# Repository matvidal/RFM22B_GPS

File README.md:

# RFM22B_GPS
In this repository you can find multiple tests using the transceiver RFM22B and the L80 GPS. Given that both devices use a logic level of 3.3 V, they are both connected to an Arduino Due board. 

The echo test is used to try different combinations of bit rate and modulation at different distances and analize which combination permorms better. The purpose of the GPS test is to determine which is the maximum distance that this transceiver can reach with uncorrupted data using the best configuration obtained before. In order to do that, a GPS is added to obtain at what distance the communication link is lost.

The GPS test consists on using a radiosonde to transport one Arduino Due, one GPS L80 and one RFM22B acting as a transmiter. On the ground there will be three RFM22B with arduinos to receive the data from the GPS. One will use an omnidirectional antenna, another a personal Yagi antenna, and the third will be connected to the Earth Station of the Department of Electrical Engineering of Universidad de Chile.

## Code
In this folder you will find some tests you can run using the Radiohead library for the transceiver and the TinyGPS+ library for the GPS.

### Chat test
Two Arduinos are hooked up to two different computers. Using the serial monitor, two persons can write messages to each other and send them using the transceiver RFM22B.

### Normal test
One transceiver is the transmiter and the other the receiver. Random packets are sent continually from TX to RX. If there is no confirmation of the packet being received correctly by the RX, an error message is printed on screen.

### Echo test
In this test, one Arduino generates 1000 packets of random data and transmit it to another Arduino. Then, the receiver only retransmit the same packet to the TX. The TX compares the data generated and the packet received and evaluates if they are the same and use a counter to save the number of successes.
 
### GPS test

The transmiter with the microcontroler and the GPS is transported by a balloon with helium. It transmit the data adquired by the GPS to three different receivers.

## Doc
All the datasheets of the components used are in this folder. There is also an .ods file with the results of the radiosonde test.

## Hardware
Here there are all the designs of the shields to plug the breakout board of the RFM22B to the Arduino Due, the GPS with the TRX and the arduino and the RFM23BP transceiver to also an Arduino Due.

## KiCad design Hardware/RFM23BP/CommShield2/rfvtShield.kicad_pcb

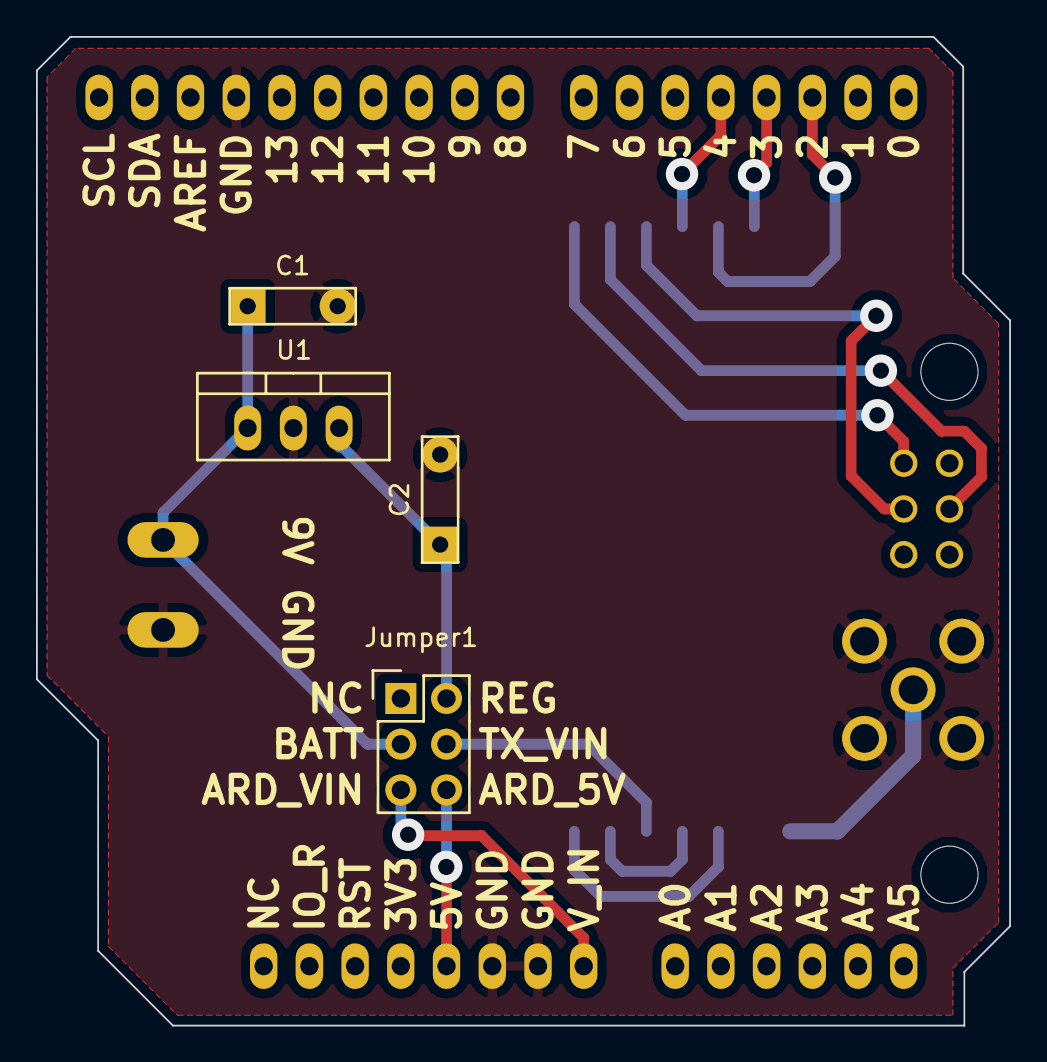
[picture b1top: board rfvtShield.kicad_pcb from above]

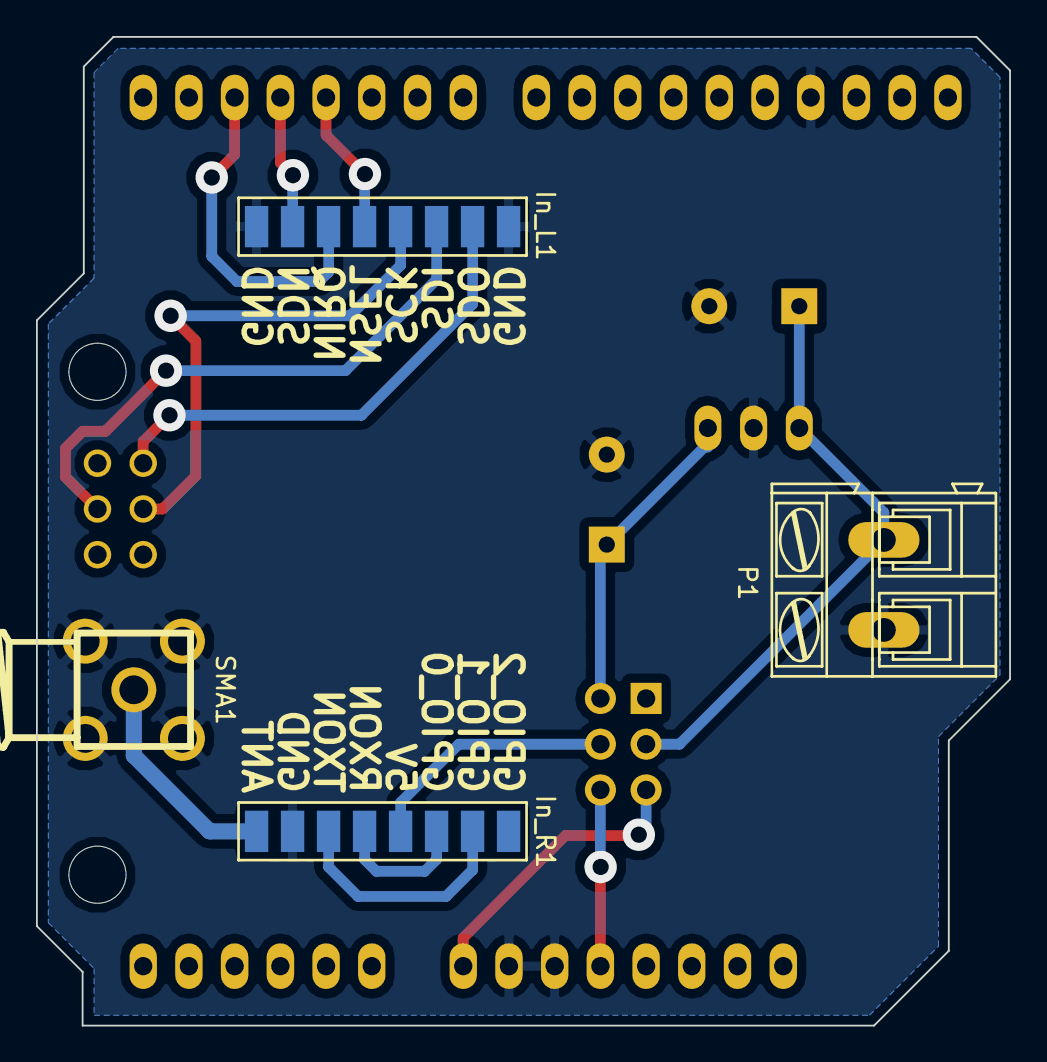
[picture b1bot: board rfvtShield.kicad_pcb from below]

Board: 2 copper layers, 54.1 x 54.9 mm, 9 parts (4 on the bottom side), 15 nets.

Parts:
C1, C2: C; C_Rect_L7_W2_P5
In_L1: CONN_01X08; Pin_Header_1x08
In_R1: CONN_01X08; Pin_Header_1x08
Jumper1: CONN_01X06; Pin_Header_Straight_2x03
P1: CONN_01X02; AK300-2
SHIELD1: ARDUINO_SHIELD
SMA1: CONN_01X05; SMA
U1: 7805; TO-220_Neutral123_Vertical

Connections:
/ANT: In_R1.8, SMA1.1
/ARD_5V: Jumper1.6, SHIELD1.5V
/ARD_VIN: Jumper1.5, SHIELD1.V_IN
/BATT: C1.1, Jumper1.3, P1.2, U1.1
/GPIO_0: In_R1.3, In_R1.5
/GPIO_1: In_R1.2, In_R1.6
/NIRQ: In_L1.6, SHIELD1.2
/NSEL: In_L1.5, SHIELD1.4
/REG: C2.1, Jumper1.2, U1.3
/SCK: In_L1.4, SHIELD1.SP3
/SDI: In_L1.3, SHIELD1.SP4
/SDN: In_L1.7, SHIELD1.3
/SDO: In_L1.2, SHIELD1.SP1
/TX_VIN: In_R1.4, Jumper1.4
GND: C1.2, C2.2, In_L1.1, In_L1.8, In_R1.7, P1.1, SHIELD1.GND1, SHIELD1.GND2, SHIELD1.GND3, SMA1.2, SMA1.3, SMA1.4, SMA1.5, U1.2

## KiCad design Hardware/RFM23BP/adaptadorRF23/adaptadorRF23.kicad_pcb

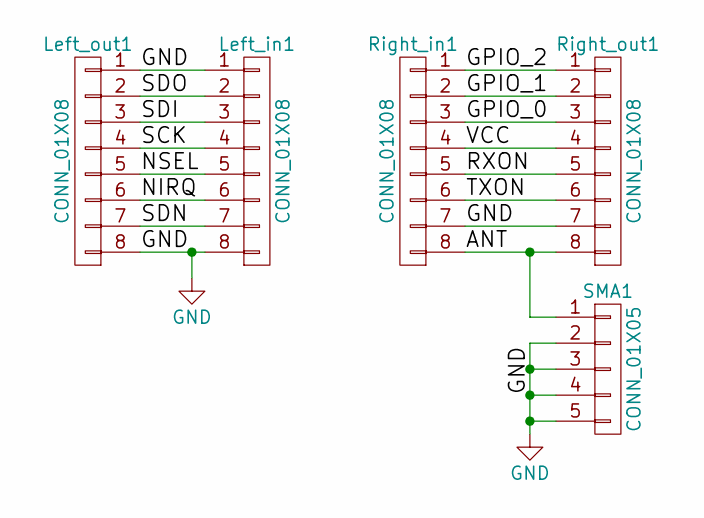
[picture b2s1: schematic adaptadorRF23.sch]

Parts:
Left_in1: CONN_01X08; Pin_Header_1x08
Left_out1: CONN_01X08; Pin_Header_Straight_1x08
Right_in1: CONN_01X08; Pin_Header_1x08
Right_out1: CONN_01X08; Pin_Header_Straight_1x08
SMA1: CONN_01X05; SMA

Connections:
/ANT: Right_in1.8, Right_out1.8, SMA1.1
/GPIO_0: Right_in1.3, Right_out1.3
/GPIO_1: Right_in1.2, Right_out1.2
/GPIO_2: Right_in1.1, Right_out1.1
/NIRQ: Left_in1.6, Left_out1.6
/NSEL: Left_in1.5, Left_out1.5
/RXON: Right_in1.5, Right_out1.5
/SCK: Left_in1.4, Left_out1.4
/SDI: Left_in1.3, Left_out1.3
/SDN: Left_in1.7, Left_out1.7
/SDO: Left_in1.2, Left_out1.2
/TXON: Right_in1.6, Right_out1.6
/VCC: Right_in1.4, Right_out1.4
GND: Left_in1.1, Left_in1.8, Left_out1.1, Left_out1.8, Right_in1.7, Right_out1.7, SMA1.2, SMA1.3, SMA1.4, SMA1.5

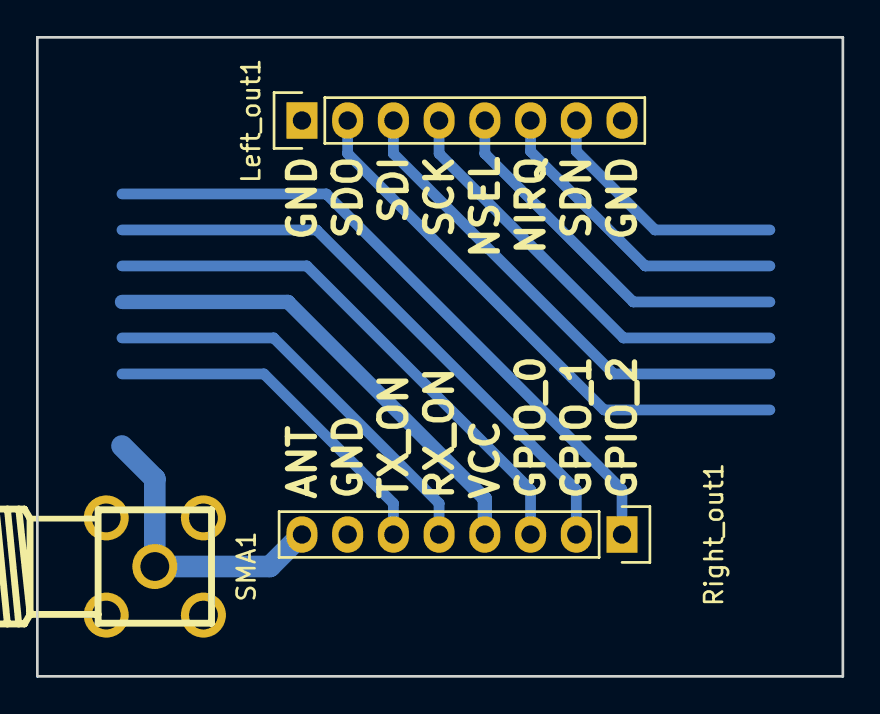
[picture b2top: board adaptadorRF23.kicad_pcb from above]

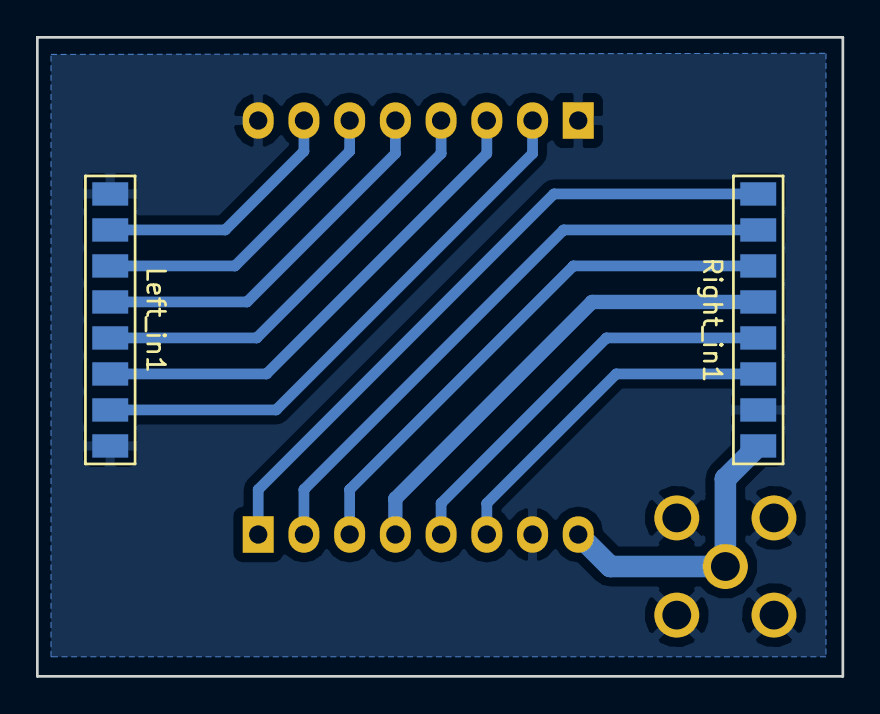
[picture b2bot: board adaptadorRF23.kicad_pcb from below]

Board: 2 copper layers, 44.8 x 35.5 mm, 5 parts (2 on the bottom side), 14 nets.

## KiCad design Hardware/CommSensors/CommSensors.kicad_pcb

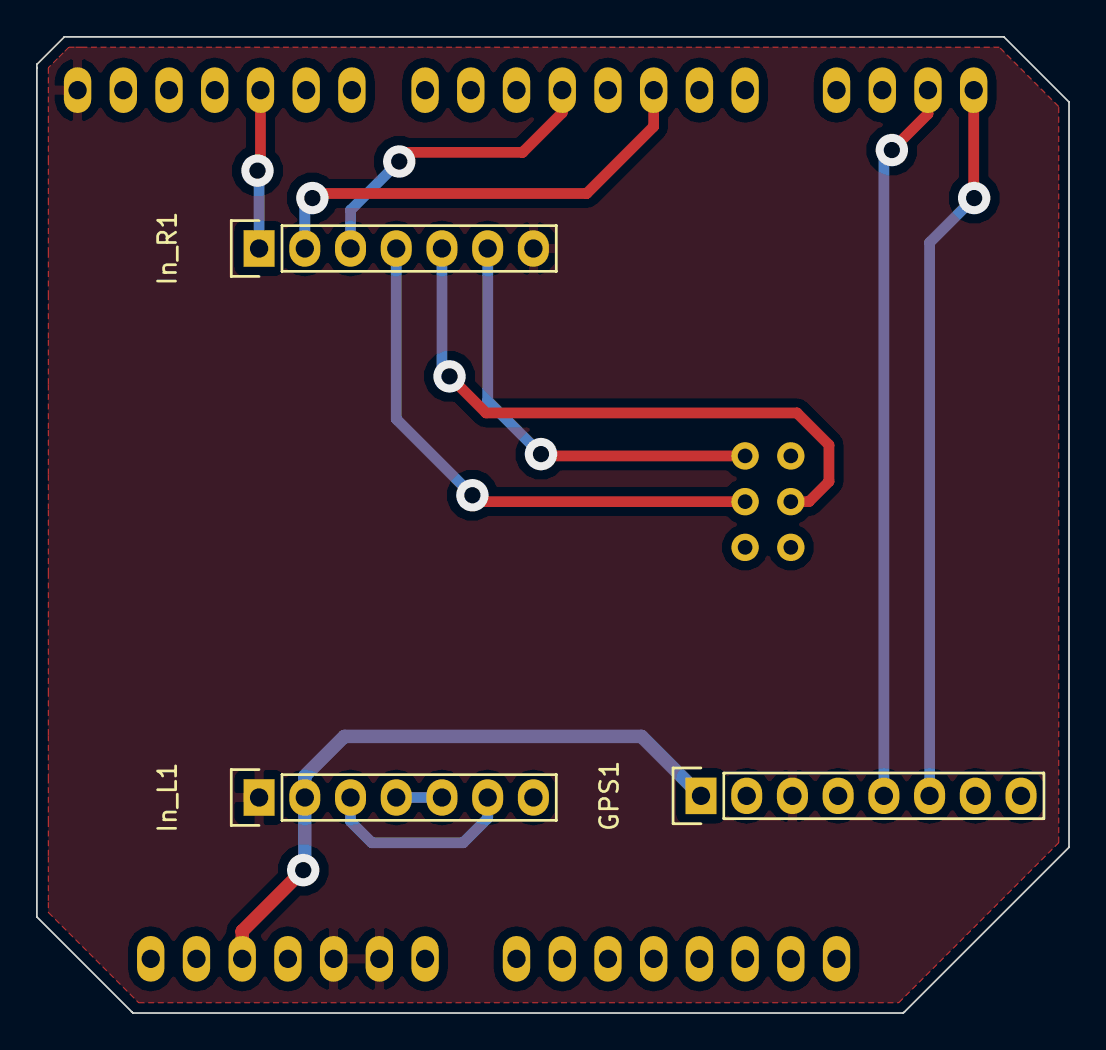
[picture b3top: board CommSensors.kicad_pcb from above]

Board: 2 copper layers, 57.3 x 54.2 mm, 4 parts (0 on the bottom side), 12 nets.

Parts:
CommSensors1: ARDUINO_DUE_SHIELD
GPS1: CONN_01X08; Pin_Header_Straight_1x08
In_L1: CONN_01X07; Pin_Header_Straight_1x07
In_R1: CONN_01X07; Pin_Header_Straight_1x07

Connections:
/3V3: CommSensors1.3V3, GPS1.1, In_L1.2
/GPIO_0: In_L1.4, In_L1.5
/GPIO_1: In_L1.3, In_L1.6
/NIRQ: CommSensors1.2, In_R1.2
/NSEL: CommSensors1.4, In_R1.3
/RX: CommSensors1.16, GPS1.5
/SCK: CommSensors1.SP3, In_R1.4
/SDI: CommSensors1.SP4, In_R1.5
/SDN: CommSensors1.10, In_R1.1
/SDO: CommSensors1.SP1, In_R1.6
/TX: CommSensors1.17, GPS1.6
GND: CommSensors1.GND1, CommSensors1.GND2, CommSensors1.GND3, GPS1.3, In_L1.1, In_R1.7

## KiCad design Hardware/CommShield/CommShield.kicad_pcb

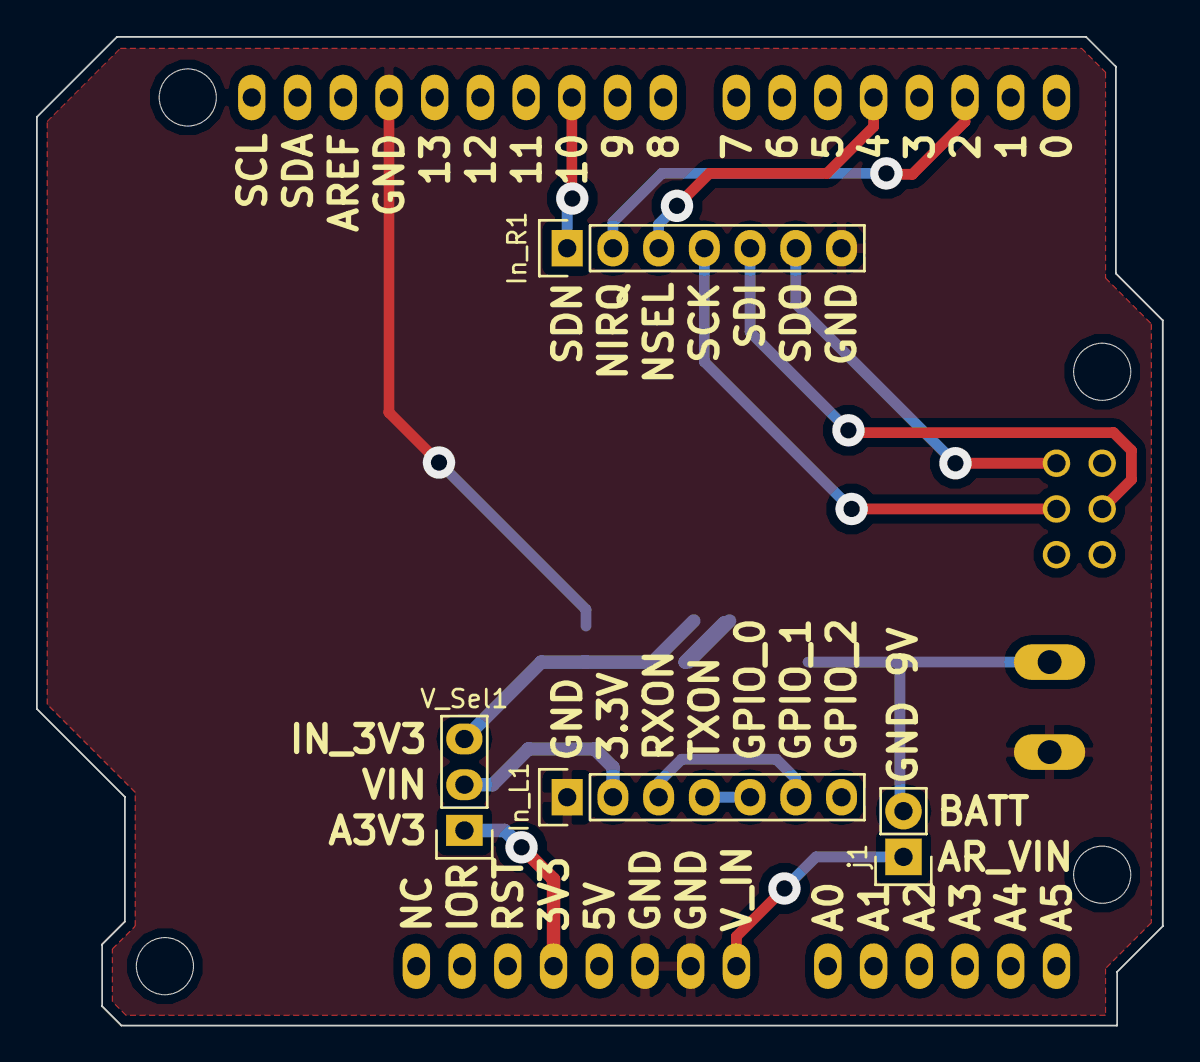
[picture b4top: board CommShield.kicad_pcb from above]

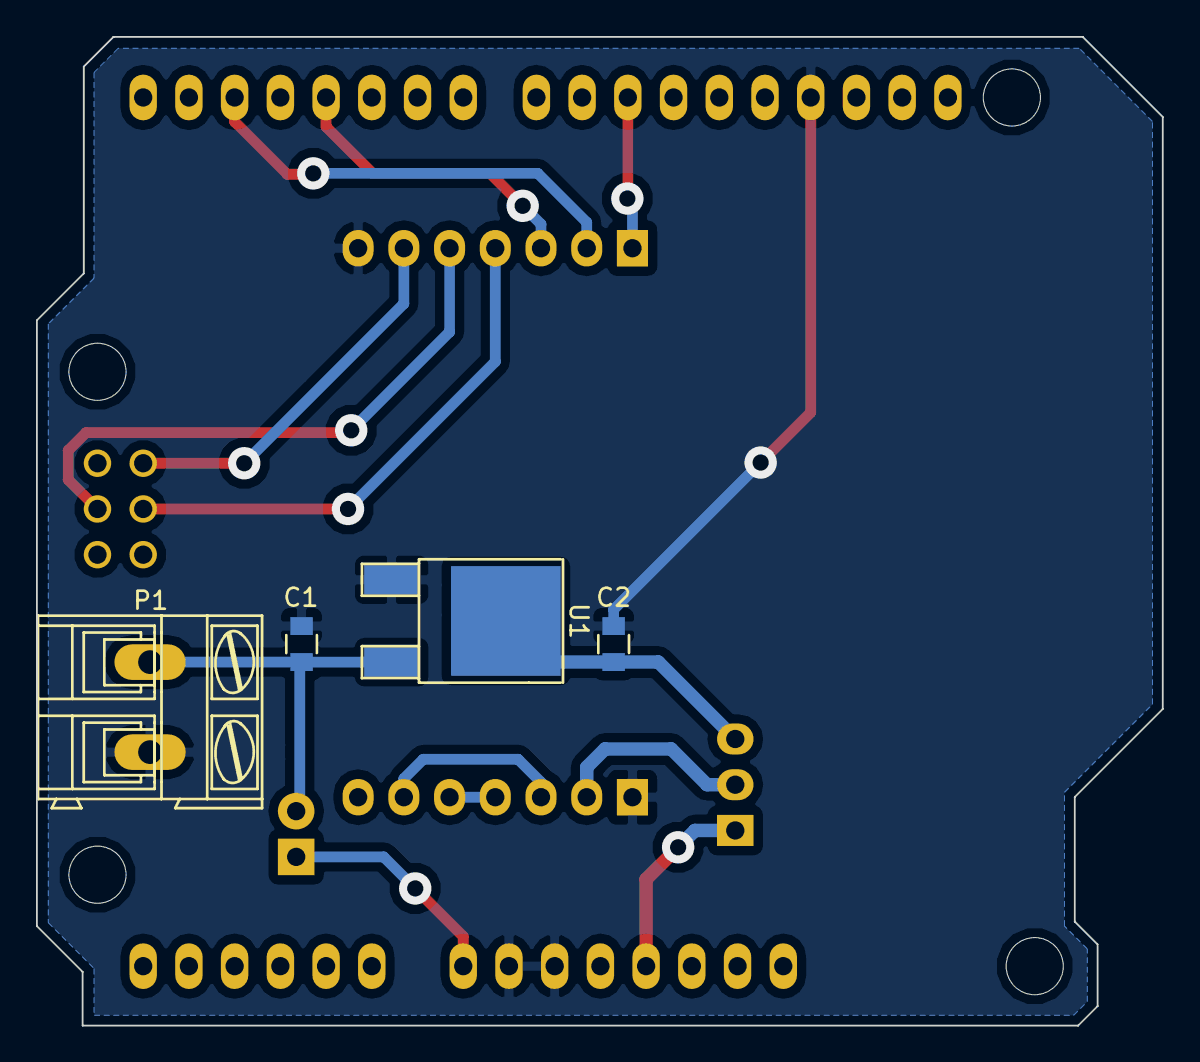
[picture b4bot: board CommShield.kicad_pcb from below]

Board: 2 copper layers, 62.5 x 54.9 mm, 9 parts (4 on the bottom side), 14 nets.

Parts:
C1, C2: C; C_0805
In_L1: CONN_01X07; Pin_Header_Straight_1x07
In_R1: CONN_01X07; Pin_Header_Straight_1x07
P1: CONN_01X02; AK300-2
SHIELD1: ARDUINO_SHIELD
U1: AP1117D33; TO-252-2Lead
V_Sel1: CONN_01X03; Socket_Strip_Straight_1x03
j1: CONN_01X02; Pin_Header_Straight_1x02

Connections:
/3.3V: C2.1, U1.2, V_Sel1.3
/A3V3: SHIELD1.3V3, V_Sel1.1
/ARD_VIN: SHIELD1.V_IN, j1.1
/BATT: C1.1, P1.1, U1.3, j1.2
/GPIO_0: In_L1.4, In_L1.5
/GPIO_1: In_L1.3, In_L1.6
/NIRQ: In_R1.2, SHIELD1.2
/NSEL: In_R1.3, SHIELD1.4
/SCK: In_R1.4, SHIELD1.SP3
/SDI: In_R1.5, SHIELD1.SP4
/SDN: In_R1.1, SHIELD1.10
/SDO: In_R1.6, SHIELD1.SP1
/Vin: In_L1.2, V_Sel1.2
GND: C1.2, C2.2, In_L1.1, In_R1.7, P1.2, SHIELD1.GND1, SHIELD1.GND2, SHIELD1.GND3, U1.1

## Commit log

2016-05-11 Se agrega carpeta Hardware
2016-05-11 Code added
2016-05-11 Arduino file order added
2016-05-11 Better folder's order and libraries added
2016-05-17 Unidirectional communication test added
2016-05-18 Azimuth and elevation calculations added
2016-05-19 Added the display on serial monitor of the Azimuth and the Elevation for the Earth Station. Some delays are reduced, and the tabulation for some functions is changed to 4.
2016-05-20 Code order and some descriptions translated to english
2016-05-20 More translation to english and code order
2016-05-20 The external library (freetronics) has it's own folder, and the shield for the RFM23BP is added
2016-05-20 Minor changes
2016-05-23 Added a function to calculate the distance in space (XYZ) between the transmiter and the receiver. Added more documentation on azimuth, elevation and coord_distance functions. These new features are 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
2016-05-30 CommSensors improved plus minor changes in the code.
2016-05-30 Distance calculation added to the Earth Station.
2016-05-31 Added abbreviations in the displayInfo function, so that it does not print in a new line for the same set of information. Also added de calculations for the azimuth and the elevation for de Yagi and 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
2016-05-31 Trying to create a library for the RX
2016-06-01 Added Doc file with the datasheets of the hardware used. \nChanged the modulation for the GPS test (GFSK to FSK). \nDeleted unnecesary variables from TX_GPS.ino.
2016-06-06 The new library is implemented on all receivers for the GPS test
2016-07-05 Delete RX.ino~
    Unnecessary file
2016-07-05 Delete TX.ino~
    Unnecessary file.
